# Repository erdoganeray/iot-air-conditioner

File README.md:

# KlimaHub: IoT Klima Kumandası ve Sıcaklık/Nem Sensörleri

ESP32 tabanlı, evdeki WiFi kopmalarına dayanıklı bir klima kontrol sistemi. Kendi kartınızı
CNC'de kazıyıp, kutusunu 3D yazıcıda basıp kurabileceğiniz şekilde, baştan sona hazır.

| Parça | Kart | Görev |
|---|---|---|
| **Hub** | Seeed XIAO ESP32-S3 | Klimaya IR ile komut verir, kumandayı öğrenir. Kendi SHT31 sensörü, kırmızı/yeşil LED, dokunmatik buton ve LiPo pili var |
| **Sensör × 2** | Seeed XIAO ESP32-C3 | Duvarda sıcaklık/nem ölçer, ESP-NOW ile hub'a gönderir. Pille 6–9 ay, USB-C ile şarj |

## Özellikler

- **WiFi kopsa da çalışır:** Sensörler ESP-NOW ile modemden bağımsız haberleşir. Klima kontrolü,
  otomasyon ve Bluetooth bağlantısı WiFi olmadan devam eder. Hub WiFi'a hiç vazgeçmeden yeniden
  bağlanmayı dener.
- **Klima kontrolü:** Aç/kapa, mod (soğutma, ısıtma, kuru, fan, otomatik), derece, fan, kanat.
  Fujitsu dahil ≈80 klima protokolü kumandadan otomatik tanınır. Tanınmayan kumandalar ham
  kayıtla öğretilir.
- **Otomasyon:** Termostat (seçilen sensöre göre), nem için kurutma modu, haftalık
  zamanlayıcılar, kısa döngü koruması.
- **7 günlük geçmiş:** Her sensör için sıcaklık ve nem grafikleri.
- **Telefon uygulaması:** Türkçe web uygulaması. Bluetooth (her yerde) veya WiFi
  (`http://klima.local`) ile bağlanır, ana ekrana kurulabilir.
- **Telegram botu:** Dışarıdan kontrol (`/durum`, `/ac 24 sogutma`…) ve bildirimler (pil, sensör,
  elektrik kesintisi, WiFi kesintisi, otomasyon).
- **Ölçüm aralığı** her sensör için uygulamadan ayarlanır (varsayılan 10 dk).

## Nereden başlamalı

1. [docs/RAPOR.md](docs/RAPOR.md): projenin durumu ve yapılacaklar listesi
2. [docs/SATIN_ALMA.md](docs/SATIN_ALMA.md): hazır sepet (3 site, bağlantılı) ·
   [docs/MALZEME_LISTESI.md](docs/MALZEME_LISTESI.md): parçaların teknik tanımı
3. Kartlar: [pcb/fab/README.md](pcb/fab/README.md) ile fabrikaya sipariş **veya**
   [docs/CNC.md](docs/CNC.md) ile CNC'de kazıma (Candle)
4. [enclosure/README.md](enclosure/README.md): kutuların baskısı
5. [docs/MONTAJ.md](docs/MONTAJ.md): lehim ve montaj
6. [docs/KURULUM.md](docs/KURULUM.md): yazılım yükleme, WiFi, kumanda, sensörler, Telegram

Ayrıntılı tasarım: [docs/MIMARI.md](docs/MIMARI.md) · Komut arayüzü: [docs/API.md](docs/API.md)

## Klasörler

```
app/                 Web uygulaması (tek dosya PWA) + sahte hub ve test araçları
firmware/hub/        Hub yazılımı (PlatformIO, Arduino)
firmware/sensor/     Sensör yazılımı
firmware/lib/        Ortak kod: ESP-NOW protokolü, pil hesabı, SHT31 sürücüsü
firmware/bin/        Hazır yazılım dosyaları (tarayıcıdan yüklemek için)
pcb/                 KiCad kartları, üretici betikler, Gerber ve CNC (G-code) çıktıları
enclosure/           3D kutular (STL, STEP) ve CadQuery kaynak kodu
docs/                Belgeler
```

## Görseller

## Geliştirme

```bash
# Yazılım (PlatformIO)
pio run -d firmware/hub            # hub derle
pio test -d firmware/hub -e native # birim testleri
pio run -d firmware/sensor         # sensör derle

# Uygulamayı donanımsız deneme
pip install aiohttp && python3 app/tools/mock_hub.py   # http://localhost:8080, PIN 1234

# Kartlar (KiCad 7+ ve Freerouting gerekir), G-code ve montaj haritaları
python3 pcb/tools/build_pcb.py all
python3 pcb/tools/cnc.py all --angle 30 --tip 0.2
python3 pcb/tools/assembly_maps.py all
python3 pcb/tools/build_fab.py all      # fabrika (2 katman) sürümü

# Kutular (CadQuery)
python3 enclosure/build_enclosures.py
```

Her push'ta GitHub Actions iki yazılımı derler, birim testlerini ve uygulamanın tarayıcı testini
çalıştırır. `app/` değişince uygulama GitHub Pages'te yayınlanır.

**Gizli bilgiler** (WiFi şifresi, Telegram token'ı) depoya hiçbir zaman yazılmaz. Uygulamadan
cihaza girilir ve yalnızca hub'ın içinde saklanır.

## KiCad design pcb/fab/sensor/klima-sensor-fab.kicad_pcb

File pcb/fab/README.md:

# Fabrika Kartları (PCB siparişi)

CNC'de kazımak yerine kartları bir PCB fabrikasına (JLCPCB, PCBWay vb.) ürettirmek için.
Kart ölçüleri, eleman yerleşimi ve pinler CNC sürümüyle **aynıdır**: kutular, yazılım ve montaj
haritaları (`pcb/cnc/<kart>/montaj_*.png`) değişmeden geçerlidir.

| Kart | Ölçü | Sipariş dosyası |
|---|---|---|
| Hub | 54 × 42 mm | `uretim/hub/klima-hub-gerber.zip` |
| Sensör | 25 × 44 mm (yarıklı, M2 delikli) | `uretim/sensor/klima-sensor-gerber.zip` |

## CNC sürümünden farkları

- **2 katman** (üst + alt bakır), delikler metal kaplı, iki yüzde GND dolgusu ve dikiş vialar.
- İzler 0.3 mm (güç hatları 0.6 mm), boşluk 0.2 mm. Fabrikaların standart kurallarının
  rahatça içinde (en küçük delik 0.35 mm via).
- Lehim maskesi ve **serigrafi**: eleman adları, pil ve XBAT için `+`, XIAO pin adları, J3
  pin adları, IR alıcının `OUT` bacağı.
- Elemanlar aynı yüzlerde: bacaklı elemanlar üstten takılır; 1206 direnç ve kondansatörler alt
  yüze lehimlenir (alt yüzde serigrafide adları yazar, değerleri `montaj_alt.png`'de).

## Sipariş (JLCPCB örneği)

1. https://jlcpcb.com → **Order now** → zip dosyasını yükleyin. Ölçü otomatik okunur.
2. Ayarlar (gerisi varsayılan kalabilir):

| Ayar | Değer |
|---|---|
| Base Material | FR-4 |
| Layers | **2** |
| PCB Qty | 5 (en az adet; hub için 1, sensör için 2 gerekir, kalanı yedek) |
| PCB Thickness | **1.6 mm** (kutular buna göre çizildi) |
| PCB Color | İstediğiniz (yeşil en ucuz ve en hızlı) |
| Surface Finish | HASL (lead-free önerilir) |
| Outer Copper Weight | 1 oz |
| Remove Order Number | Önemli değil. "No" seçerseniz fabrika kartın bir yerine küçük bir sipariş numarası basar; "Yes" bazen ücretlidir |

3. Hub ve sensör iki ayrı tasarım olduğu için iki ayrı sipariş kalemi olur.
4. **PCBA (dizgi) gerekmez:** elemanlar elle lehimlenecek büyüklükte seçildi.

Diğer fabrikalarda da aynı zip yüklenir. Dosyalar KiCad'in standart Gerber (Protel uzantılı)
ve Excellon biçimindedir. Sensördeki yarık ve dış hat `Edge_Cuts` katmanındadır, M2 delik
`NPTH.drl` dosyasındadır.

## Yeniden üretmek

```bash
python3 pcb/tools/build_fab.py all     # KiCad 7+, Java 21, Freerouting gerekir
```

KiCad dosyaları `pcb/fab/<kart>/` klasöründedir (DRC raporu dahil). Rapordaki serigrafi
uyarıları (taşan/çakışan yazı) üretimi engellemez: fabrika serigrafiyi pedlerden ve kenardan
kırpar. Bakır hatası ve bağlanmamış hat yoktur.

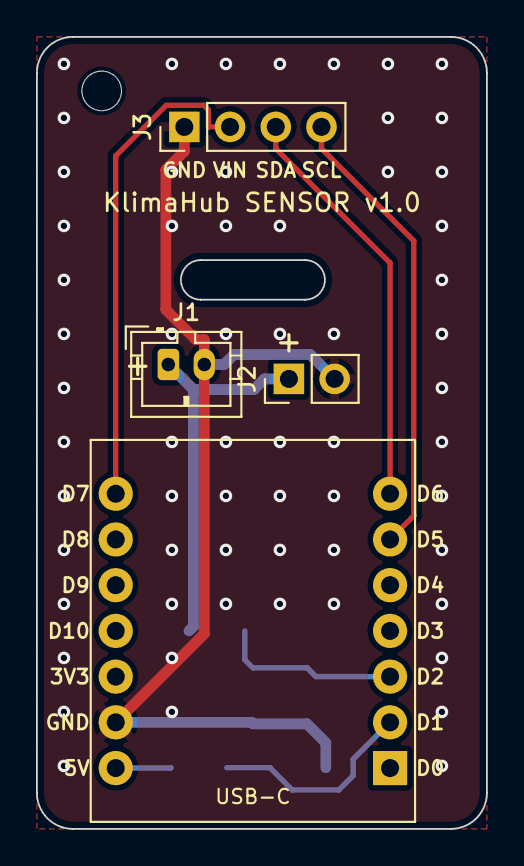
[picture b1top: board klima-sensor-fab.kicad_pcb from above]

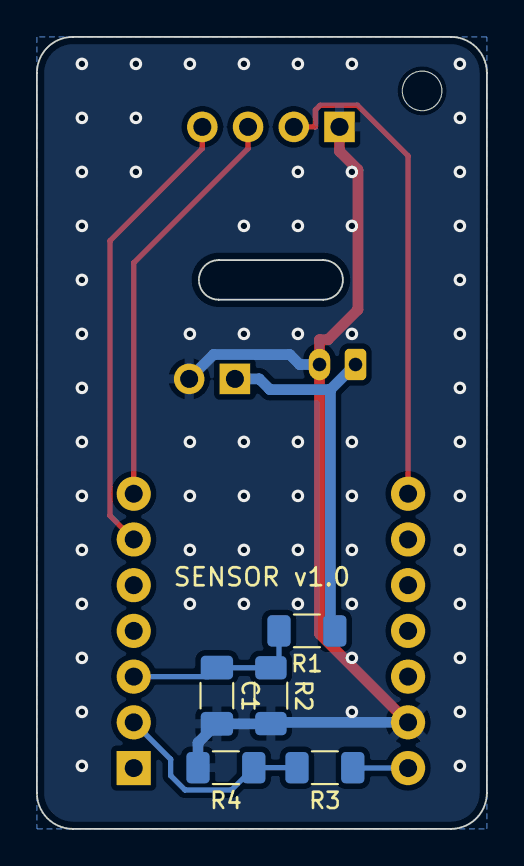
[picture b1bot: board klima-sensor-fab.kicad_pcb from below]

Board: 2 copper layers, 25.0 x 44.0 mm, 10 parts (5 on the bottom side), 8 nets.

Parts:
C1: 100nF; C_1206_3216Metric_Pad1.33x1.80mm_HandSolder
H1: M2; MountingHole_2.2mm_M2
J1: BAT; JST_PH_B2B-PH-K_1x02_P2.00mm_Vertical
J2: XBAT; PinHeader_1x02_P2.54mm_Vertical
J3: SHT31; PinHeader_1x04_P2.54mm_Vertical
R1, R2: 470k; R_1206_3216Metric_Pad1.30x1.75mm_HandSolder
R3: 100k; R_1206_3216Metric_Pad1.30x1.75mm_HandSolder
R4: 150k; R_1206_3216Metric_Pad1.30x1.75mm_HandSolder
U1: XIAO ESP32-C3; XIAO_DIP14

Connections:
BAT_SENSE: C1.1, R1.2, R2.1, U1.3
GND: C1.2, J1.2, J2.2, J3.1, R2.2, R4.2, U1.13
SCL: J3.4, U1.6
SDA: J3.3, U1.7
SENS_PWR: J3.2, U1.8
USB_SENSE: R3.2, R4.1, U1.2
VBAT: J1.1, J2.1, R1.1
VBUS: R3.1, U1.14

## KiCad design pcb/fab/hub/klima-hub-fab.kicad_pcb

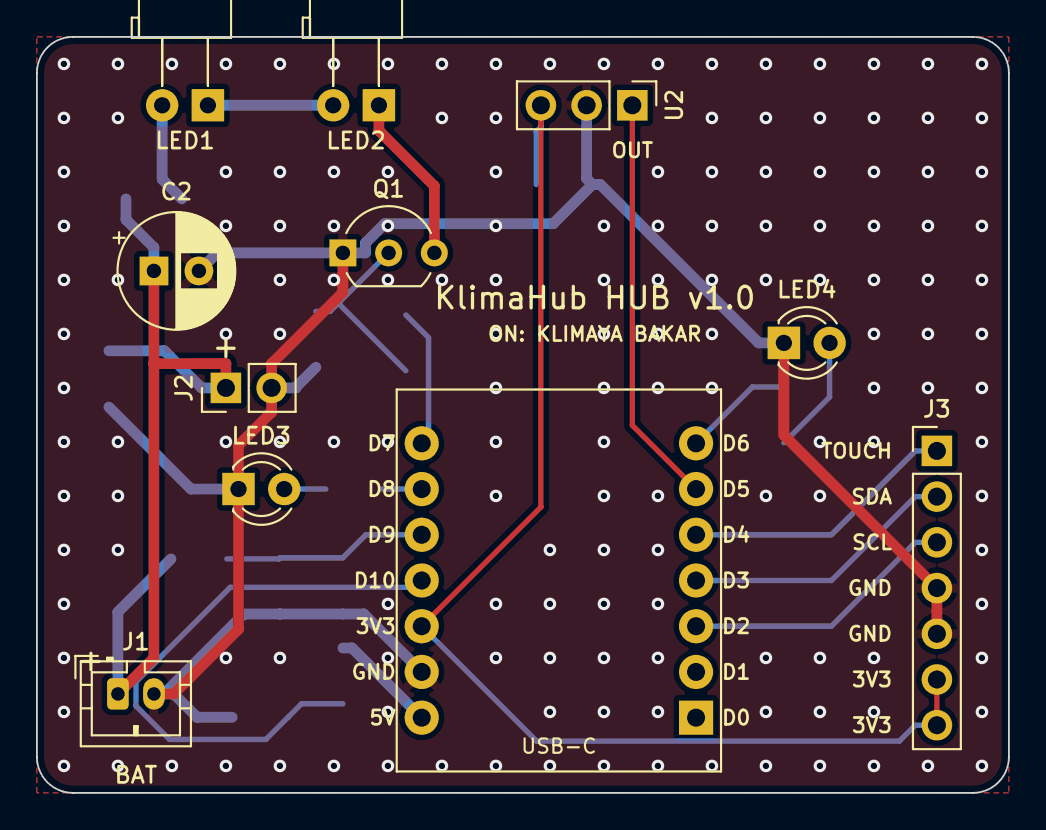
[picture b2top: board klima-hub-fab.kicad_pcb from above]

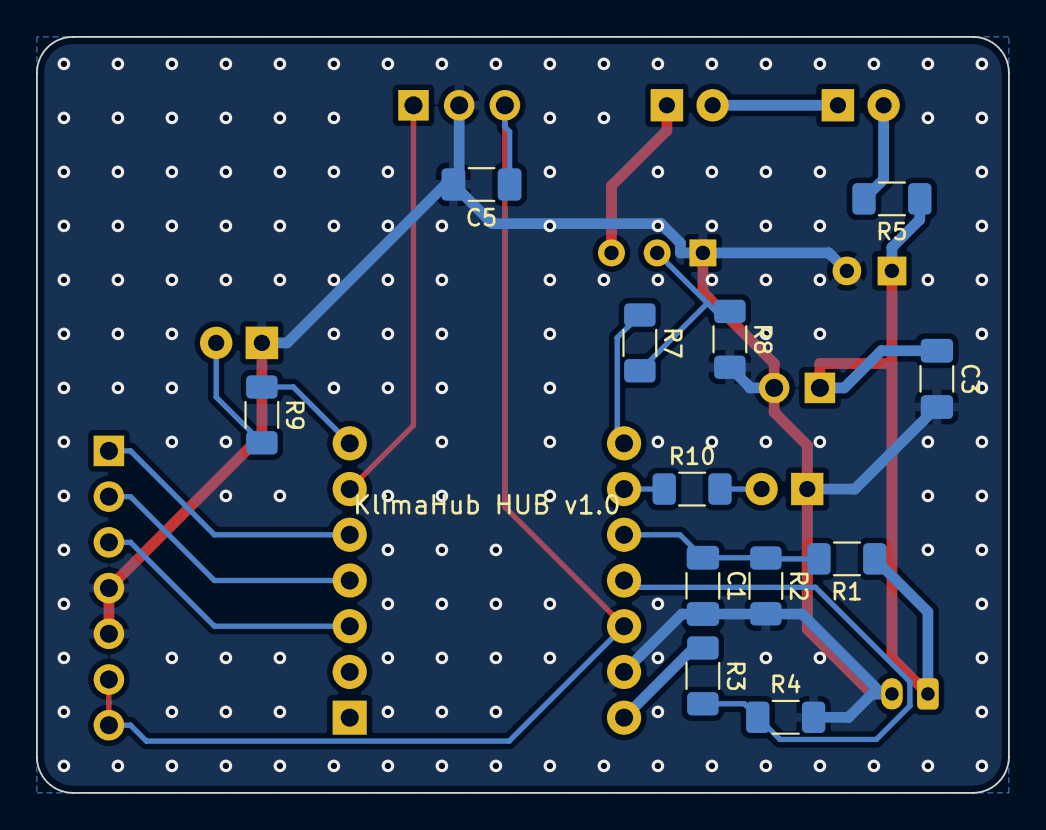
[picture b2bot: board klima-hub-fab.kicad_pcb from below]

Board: 2 copper layers, 54.0 x 42.0 mm, 23 parts (12 on the bottom side), 19 nets.

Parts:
C1, C3, C5: 100nF; C_1206_3216Metric_Pad1.33x1.80mm_HandSolder
C2: 220uF 10V; CP_Radial_D6.3mm_P2.50mm
J1: BAT; JST_PH_B2B-PH-K_1x02_P2.00mm_Vertical
J2: XBAT; PinHeader_1x02_P2.54mm_Vertical
J3: MODUL; PinHeader_1x07_P2.54mm_Vertical
LED1, LED2: IR 940nm 5mm; LED_D5.0mm_Horizontal_O3.81mm_Z3.0mm
LED3: Kirmizi 3mm; LED_D3.0mm
LED4: Yesil 3mm; LED_D3.0mm
Q1: S8050; TO-92_Inline_Wide
R1, R2: 220k; R_1206_3216Metric_Pad1.30x1.75mm_HandSolder
R3: 100k; R_1206_3216Metric_Pad1.30x1.75mm_HandSolder
R4: 150k; R_1206_3216Metric_Pad1.30x1.75mm_HandSolder
R5: 10R; R_1206_3216Metric_Pad1.30x1.75mm_HandSolder
R7: 150R; R_1206_3216Metric_Pad1.30x1.75mm_HandSolder
R8: 10k; R_1206_3216Metric_Pad1.30x1.75mm_HandSolder
R9, R10: 470R; R_1206_3216Metric_Pad1.30x1.75mm_HandSolder
U1: XIAO ESP32-S3; XIAO_DIP14
U2: VS1838B; PinHeader_1x03_P2.54mm_Vertical

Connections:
+3V3: C5.1, J3.6, J3.7, U1.12, U2.3
BAT_SENSE: C1.1, R1.2, R2.1, U1.10
GND: C1.2, C2.2, C3.2, C5.2, J1.2, J2.2, J3.4, J3.5, LED3.1, LED4.1, Q1.1, R2.2, R4.2, R8.2, U1.13, U2.2
IR_K: LED2.1, Q1.3
IR_MID: LED1.1, LED2.2
IR_RX: U1.6, U2.1
IR_TX: R7.1, U1.8
LED1_A: LED1.2, R5.2
LEDG: LED4.2, R9.2
LEDG_A: R9.1, U1.7
LEDR: LED3.2, R10.2
LEDR_A: R10.1, U1.9
Q1_B: Q1.2, R7.2, R8.1
SCL: J3.3, U1.3
SDA: J3.2, U1.4
TOUCH: J3.1, U1.5
USB_SENSE: R3.2, R4.1, U1.11
VBAT: C2.1, C3.1, J1.1, J2.1, R1.1, R5.1
VBUS: R3.1, U1.14

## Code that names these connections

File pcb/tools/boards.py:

"""Hub ve sensör kartlarının tanımı: kart ölçüsü, eleman yerleşimi ve bağlantı listesi.

Koordinatlar KiCad üst görünümündedir (mm): X sağa, Y aşağıya, (0,0) kartın sol-üst köşesi.
Tek yüzlü kart: bakır ALT yüzde (B.Cu). Bacaklı (THT) elemanlar üstten takılır, alttan
lehimlenir. SMD elemanlar (1206 direnç/kondansatör, SMA diyot) doğrudan alt yüze lehimlenir.

Hub: ön kenar (y=0) klimaya bakar; IR LED'ler, IR alıcı ve durum LED'leri buradadır.
     XIAO'nun USB-C'si arka kenara (y=max) bakar.
Sensör: duvarda dikey durur. Üst kenarda SHT31 (ısıl yarıkla ayrılmış), alt kenarda USB-C.
        Sol üst köşedeki M2 delik kutunun vidası içindir.
"""

FP = "/usr/share/kicad/footprints"
LOCAL = "klima"  # pcb/lib/klima.pretty

R1206 = ("Resistor_SMD", "R_1206_3216Metric_Pad1.30x1.75mm_HandSolder")
C1206 = ("Capacitor_SMD", "C_1206_3216Metric_Pad1.33x1.80mm_HandSolder")
SMA = ("Diode_SMD", "D_SMA_Handsoldering")
CP63 = ("Capacitor_THT", "CP_Radial_D6.3mm_P2.50mm")
TO92W = ("Package_TO_SOT_THT", "TO-92_Inline_Wide")
LED3 = ("LED_THT", "LED_D3.0mm_Horizontal_O3.81mm_Z2.0mm")
LED5 = ("LED_THT", "LED_D5.0mm_Horizontal_O3.81mm_Z3.0mm")
LED3V = ("LED_THT", "LED_D3.0mm")
JST2 = ("Connector_JST", "JST_PH_B2B-PH-K_1x02_P2.00mm_Vertical")
H2 = ("Connector_PinHeader_2.54mm", "PinHeader_1x02_P2.54mm_Vertical")
H3 = ("Connector_PinHeader_2.54mm", "PinHeader_1x03_P2.54mm_Vertical")
H4 = ("Connector_PinHeader_2.54mm", "PinHeader_1x04_P2.54mm_Vertical")
H7 = ("Connector_PinHeader_2.54mm", "PinHeader_1x07_P2.54mm_Vertical")
XIAO = (LOCAL, "XIAO_DIP14")
MH2 = ("MountingHole", "MountingHole_2.2mm_M2")


def comp(ref, fp, value, x, y, rot=0, side="top", desc=""):
    return dict(ref=ref, fp=fp, value=value, x=x, y=y, rot=rot, side=side, desc=desc)


# --------------------------------------------------------------------- HUB
# XIAO ESP32-S3 merkezi (29, 30.2), 180° döndürülmüş: USB arkaya (+Y), USB-C yüzü kart kenarında.
#  sol sütun x=21.38: D7(22.58) D8(25.12) D9(27.66) D10(30.2) 3V3(32.74) GND(35.28) 5V(37.82)
#  sağ sütun x=36.62: D6(22.58) D5(25.12) D4(27.66) D3(30.2)  D2(32.74)  D1(35.28) D0(37.82)
# Pin görevleri tek yüzlü yönlendirme için seçildi (firmware/hub/src/pins.h ile aynı):
#  sol: D7=IR_TX, D8=LED_R, D9=BAT_SENSE, D10=USB_SENSE
#  sağ: D6=LED_G, D5=IR_RX, D4=TOUCH, D3=SDA, D2=SCL
# IR LED'leri seri bağlı ve doğrudan pilden (VBAT) beslenir: VBAT -> R5 -> LED1 -> LED2 -> Q1.
# Kart kenarında sürekli GND halkası vardır (tek yüzde GND'nin her bölgeye ulaşması için).
HUB = dict(
    name="klima-hub",
    title="KlimaHub - Hub karti (XIAO ESP32-S3)",
    width=54.0,
    height=42.0,
    corner=2.0,
    slots=[],
    gnd_ring=1.0,
    components=[
        comp("U1", XIAO, "XIAO ESP32-S3", 29.0, 30.2, 180, desc="Seeed XIAO ESP32-S3"),
        # Ön sıra: IR LED gövdeleri ön kenardan dışarı, ön duvardaki deliklere (bacaklar 90° bükülür)
        comp("LED1", LED5, "IR 940nm 5mm", 9.5, 3.8, 180, desc="IR verici LED"),
        comp("LED2", LED5, "IR 940nm 5mm", 19.0, 3.8, 180, desc="IR verici LED"),
        # Dik takılır, kubbe öne bakar. Önde durup bakan kişinin solu kartın +x yönüdür:
        # soldan sağa OUT (x=33.08), GND, VCC (x=28.0) — VS1838B'nin bacak sırasıyla aynı
        comp("U2", H3, "VS1838B", 33.08, 3.8, 270, desc="IR alıcı (OUT, GND, VCC), dik, kubbe öne"),
        # Durum LED'leri dik durur, üst kapaktaki deliklerden görünür
        comp("LED3", LED3V, "Kirmizi 3mm", 11.2, 25.12, 0, desc="Durum LED'i (kırmızı)"),
        comp("LED4", LED3V, "Yesil 3mm", 41.5, 17.0, 0, desc="Durum LED'i (yeşil)"),
        comp("J3", H7, "MODUL", 50.0, 23.0, 0,
             desc="Modül konnektörü: TOUCH, SDA, SCL, GND, GND, 3V3, 3V3 (TTP223 + SHT31)"),
        comp("Q1", TO92W, "S8050", 17.0, 12.0, 0, desc="IR LED sürücü NPN (E-B-C)"),
        comp("C2", CP63, "220uF 10V", 6.5, 13.0, 0, desc="IR besleme tamponu"),
        comp("J1", JST2, "BAT", 4.5, 36.5, 0, desc="LiPo pil 503035 (JST-PH 2.0)"),
        comp("J2", H2, "XBAT", 10.5, 19.5, 90, desc="XIAO alt BAT+/BAT- pedlerine kablo"),
        # SMD (alt yüz)
        comp("C3", C1206, "100nF", 4.0, 19.0, 90, "bottom", "VBAT dekuplaj"),
        comp("R5", R1206, "10R", 6.5, 9.0, 0, "bottom", "IR LED akım (seri)"),
        comp("R7", R1206, "150R", 20.5, 17.0, 90, "bottom", "Q1 baz"),
        comp("R8", R1206, "10k", 15.5, 16.8, 90, "bottom", "Q1 baz pull-down"),
        comp("R9", R1206, "470R", 41.5, 21.0, 90, "bottom", "Yeşil LED"),
        comp("R10", R1206, "470R", 17.6, 25.12, 180, "bottom", "Kırmızı LED"),
        comp("C5", C1206, "100nF", 29.3, 8.2, 0, "bottom", "IR alıcı dekuplaj"),
        comp("R1", R1206, "220k", 9.0, 29.0, 0, "bottom", "Pil bölücü üst"),
        comp("R2", R1206, "220k", 13.5, 30.5, 90, "bottom", "Pil bölücü alt"),
        comp("C1", C1206, "100nF", 17.0, 30.5, 90, "bottom", "Pil ADC filtresi"),
        comp("R3", R1206, "100k", 17.0, 35.5, 90, "bottom", "USB bölücü üst"),
        comp("R4", R1206, "150k", 12.4, 37.8, 180, "bottom", "USB bölücü alt"),
    ],
    nets={
        "GND": ["U1.13", "J1.2", "J2.2", "J3.4", "J3.5", "Q1.1", "R2.2", "R4.2", "R8.2",
                "C1.2", "C2.2", "C3.2", "C5.2", "LED3.1", "LED4.1", "U2.2"],
        "+3V3": ["U1.12", "J3.6", "J3.7", "U2.3", "C5.1"],
        "VBUS": ["U1.14", "R3.1"],
        "VBAT": ["J1.1", "J2.1", "R1.1", "C2.1", "C3.1", "R5.1"],
        "BAT_SENSE": ["R1.2", "R2.1", "C1.1", "U1.10"],
        "USB_SENSE": ["R3.2", "R4.1", "U1.11"],
        "IR_TX": ["U1.8", "R7.1"],
        "Q1_B": ["R7.2", "R8.1", "Q1.2"],
        "LED1_A": ["R5.2", "LED1.2"],
        "IR_MID": ["LED1.1", "LED2.2"],
        "IR_K": ["LED2.1", "Q1.3"],
        "LEDR_A": ["U1.9", "R10.1"],
        "LEDR": ["R10.2", "LED3.2"],
        "LEDG_A": ["U1.7", "R9.1"],
        "LEDG": ["R9.2", "LED4.2"],
        "IR_RX": ["U1.6", "U2.1"],
        "TOUCH": ["U1.5", "J3.1"],
        "SDA": ["U1.4", "J3.2"],
        "SCL": ["U1.3", "J3.3"],
    },
    power_nets=["GND", "VBAT", "VBUS", "IR_K", "IR_MID", "LED1_A"],
)

# ------------------------------------------------------------------ SENSÖR
# XIAO ESP32-C3 merkezi (12, 33), 180°: USB aşağı (+Y, kartın alt kenarı)
#  sol sütun x=4.38 : 5V(40.62) GND(38.08) 3V3(35.54) D10(33.0) D9(30.46) D8(27.92) D7(25.38)
#  sağ sütun x=19.62: D0(40.62) D1(38.08) D2(35.54) D3(33.0) D4(30.46) D5(27.92) D6(25.38)
# Pin görevleri (firmware/sensor/src/main.cpp ile aynı), tek yüzde kesişmesiz olacak şekilde:
#  D7=SENS_PWR (GPIO20), D6=SDA (GPIO21), D5=SCL (GPIO7), D2=BAT_SENSE (GPIO4), D1=USB_SENSE (GPIO3)
SENSOR = dict(
    name="klima-sensor",
    title="KlimaHub - Sensor karti (XIAO ESP32-C3)",
    width=25.0,
    height=44.0,
    corner=2.0,
    # SHT31 bölgesini XIAO'dan ayıran ısıl yarık (x1, y1, x2, y2), iki yanda köprü kalır
    slots=[(8.0, 12.4, 16.0, 14.6)],
    gnd_ring=1.0,
    components=[
        comp("U1", XIAO, "XIAO ESP32-C3", 12.0, 33.0, 180, desc="Seeed XIAO ESP32-C3"),
        # Kutu vidası: arka kapaktan geçen M2 vida kartı sıkıştırır ve ön kapağı tutar (enclosure/)
        comp("H1", MH2, "M2", 3.6, 3.0, desc="M2 vida deliği (kutu)"),
        comp("J3", H4, "SHT31", 8.19, 5.0, 90, desc="SHT31 modülü: GND, VIN, SDA, SCL"),
        comp("J1", JST2, "BAT", 7.3, 18.2, 0, desc="LiPo pil 503035 (JST-PH 2.0)"),
        comp("J2", H2, "XBAT", 14.0, 19.0, 90, desc="XIAO alt BAT+/BAT- pedlerine kablo"),
        comp("R1", R1206, "470k", 10.0, 33.0, 0, "bottom", "Pil bölücü üst"),
        comp("R2", R1206, "470k", 12.0, 36.6, 90, "bottom", "Pil bölücü alt"),
        comp("C1", C1206, "100nF", 15.0, 36.6, 90, "bottom", "Pil ADC filtresi"),
        comp("R3", R1206, "100k", 9.0, 40.6, 0, "bottom", "USB bölücü üst"),
        comp("R4", R1206, "150k", 14.5, 40.6, 0, "bottom", "USB bölücü alt"),
    ],
    nets={
        "GND": ["U1.13", "J1.2", "J2.2", "J3.1", "R2.2", "R4.2", "C1.2"],
        "VBAT": ["J1.1", "J2.1", "R1.1"],
        "BAT_SENSE": ["R1.2", "R2.1", "C1.1", "U1.3"],
        "VBUS": ["U1.14", "R3.1"],
        "USB_SENSE": ["R3.2", "R4.1", "U1.2"],
        "SENS_PWR": ["U1.8", "J3.2"],
        "SDA": ["U1.7", "J3.3"],
        "SCL": ["U1.6", "J3.4"],
    },
    power_nets=["GND", "VBAT"],
)

BOARDS = {"hub": HUB, "sensor": SENSOR}
